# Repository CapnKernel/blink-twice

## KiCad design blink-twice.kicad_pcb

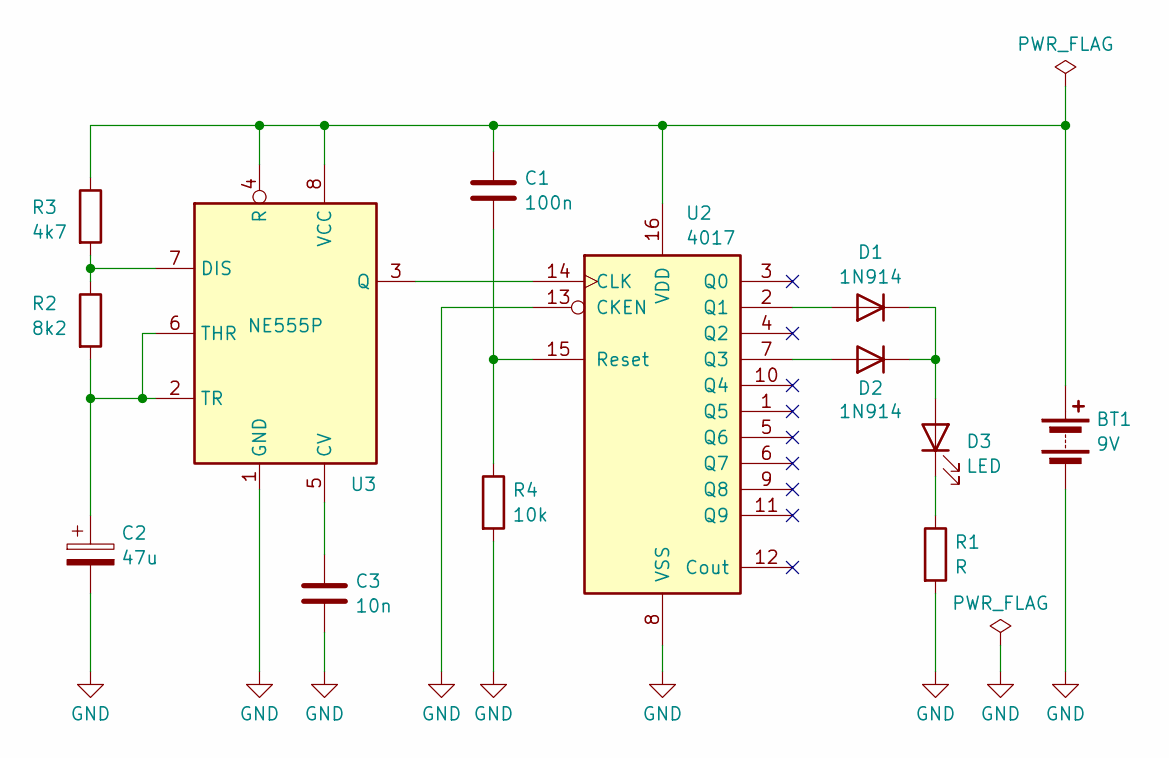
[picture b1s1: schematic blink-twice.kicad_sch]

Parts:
BT1: 9V; PinHeader_1x02_P2.54mm_Vertical
C1: 100n; C_Disc_D5.0mm_W2.5mm_P2.50mm
C2: 47u; CP_Radial_D5.0mm_P2.50mm
C3: 10n; C_Disc_D5.0mm_W2.5mm_P2.50mm
D1, D2: 1N914; D_DO-35_SOD27_P7.62mm_Horizontal
D3: LED; LED_D5.0mm
R1: R; R_Axial_DIN0207_L6.3mm_D2.5mm_P7.62mm_Horizontal
R2: 8k2; R_Axial_DIN0207_L6.3mm_D2.5mm_P7.62mm_Horizontal
R3: 4k7; R_Axial_DIN0207_L6.3mm_D2.5mm_P7.62mm_Horizontal
R4: 10k; R_Axial_DIN0207_L6.3mm_D2.5mm_P7.62mm_Horizontal
U2: 4017; DIP-16_W7.62mm
U3: NE555P; DIP-8_W7.62mm

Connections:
GND: BT1.2 (-), C2.2, C3.2, R1.2, R4.2, U2.8 (VSS), U2.13 (CKEN), U3.1 (GND)
unnamed: BT1.1 (+), C1.1, R3.1, U2.16 (VDD), U3.4 (R), U3.8 (VCC)
unnamed: D1.2 (A), U2.2 (Q1)
unnamed: D1.1 (K), D2.1 (K), D3.2 (A)
unnamed: D2.2 (A), U2.7 (Q3)
unnamed: D3.1 (K), R1.1
unnamed: U2.14 (CLK), U3.3 (Q)
unnamed: C1.2, R4.1, U2.15 (Reset)
unnamed: C3.1, U3.5 (CV)
unnamed: R2.1, R3.2, U3.7 (DIS)
unnamed: C2.1, R2.2, U3.2 (TR), U3.6 (THR)

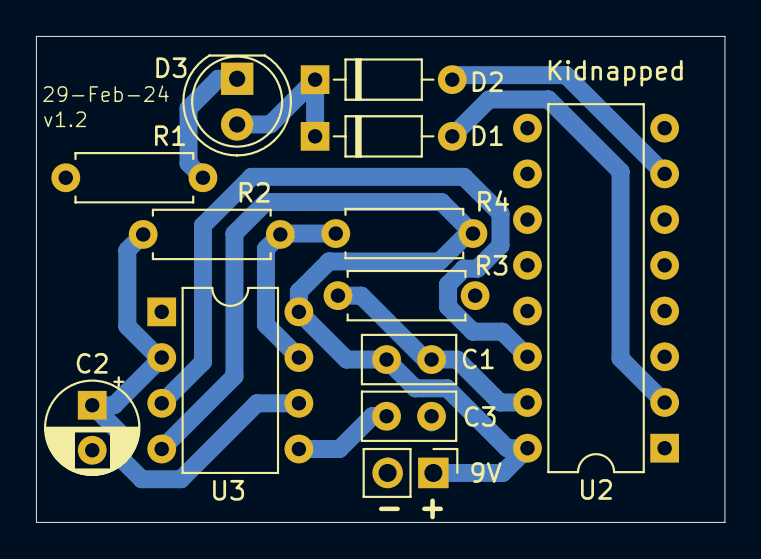
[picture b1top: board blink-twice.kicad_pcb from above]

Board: 2 copper layers, 38.2 x 27.0 mm, 13 parts (0 on the bottom side), 11 nets.

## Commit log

2024-02-28 First iteration.
2024-02-28 Groomed, and saved with KiCad 8.
